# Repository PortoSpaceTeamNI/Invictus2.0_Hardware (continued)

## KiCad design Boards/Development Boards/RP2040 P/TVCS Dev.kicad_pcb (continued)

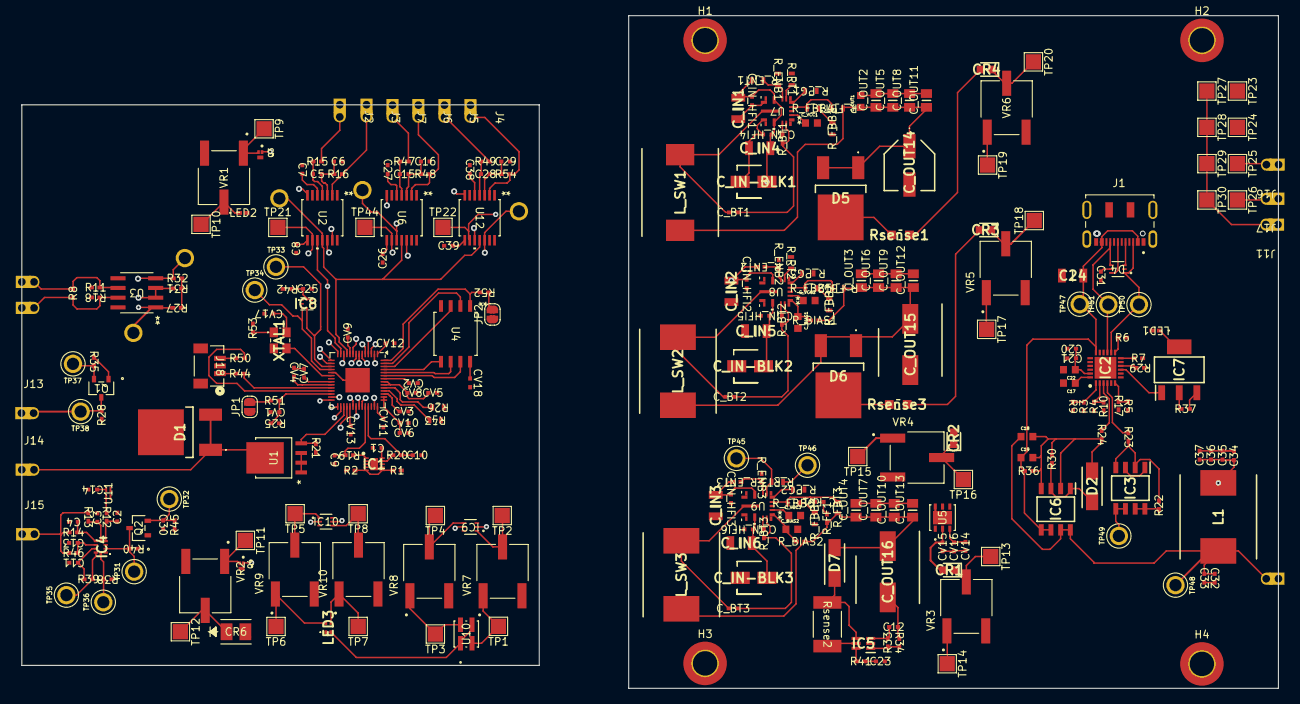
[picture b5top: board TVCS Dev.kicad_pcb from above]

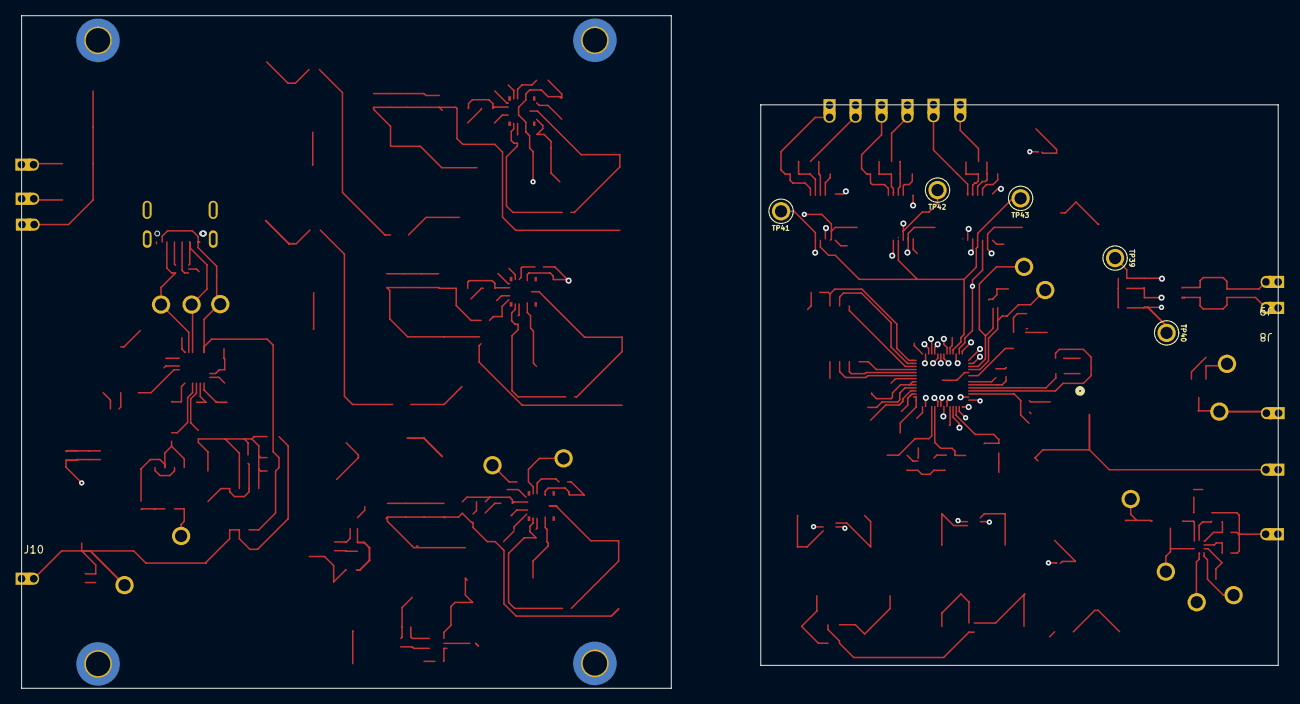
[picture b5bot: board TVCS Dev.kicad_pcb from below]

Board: 6 copper layers, 164.4 x 88.0 mm, 311 parts (8 on the bottom side), 154 nets.

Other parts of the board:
JP1, JP2: Jumper_2_Open; SolderJumper-2_P1.3mm_Open_RoundedPad1.0x1.5mm
R8: 120; RES_0402

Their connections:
/RP2040 Standard1/~RST: JP1.2 (B); also elsewhere on the board
/RP2040 Standard1/~USB_BOOT: JP2.2 (B); also elsewhere on the board
/RS_A: R8.2; also elsewhere on the board
/RS_B: R8.1; also elsewhere on the board
GND: JP1.1 (A), JP2.1 (A); also elsewhere on the board

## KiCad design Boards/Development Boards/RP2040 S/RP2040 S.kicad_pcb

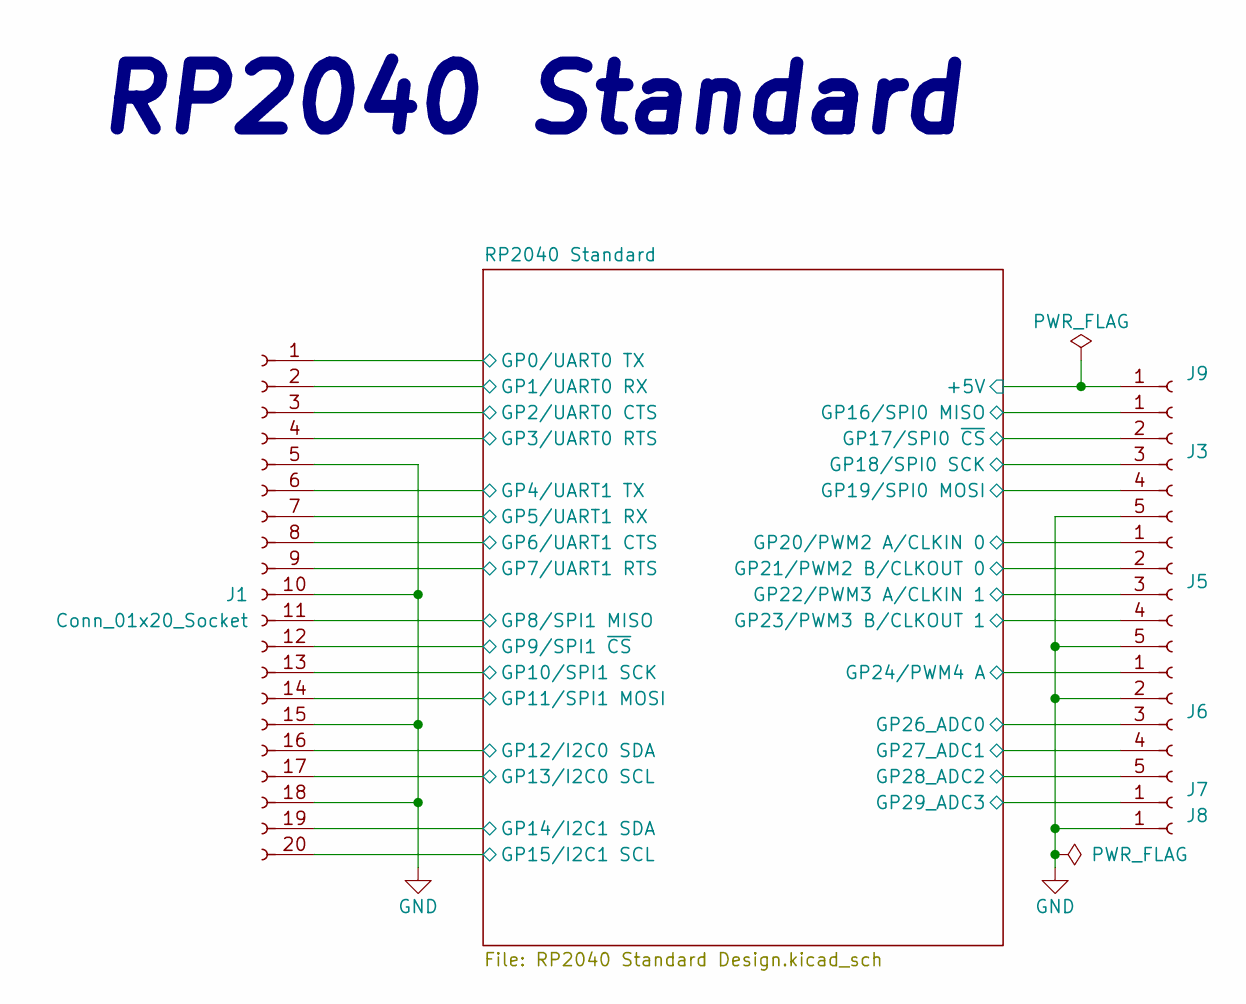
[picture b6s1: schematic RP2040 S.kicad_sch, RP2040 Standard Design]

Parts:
J1: Conn_01x20_Socket; Pico_20pin
J3, J5, J6: Conn_01x05_Socket; Pico_05pin
J7, J8, J9: Conn_01x01_Socket; Pico_01pin

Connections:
/RP2040 Standard/+5V: J9.1; also elsewhere on the board
/RP2040 Standard/GP0/UART0 TX: J1.1; also elsewhere on the board
/RP2040 Standard/GP1/UART0 RX: J1.2; also elsewhere on the board
/RP2040 Standard/GP2/UART0 CTS: J1.3; also elsewhere on the board
/RP2040 Standard/GP3/UART0 RTS: J1.4; also elsewhere on the board
/RP2040 Standard/GP4/UART1 TX: J1.6; also elsewhere on the board
/RP2040 Standard/GP5/UART1 RX: J1.7; also elsewhere on the board
/RP2040 Standard/GP6/UART1 CTS: J1.8; also elsewhere on the board
/RP2040 Standard/GP7/UART1 RTS: J1.9; also elsewhere on the board
/RP2040 Standard/GP8/SPI1 MISO: J1.11; also elsewhere on the board
/RP2040 Standard/GP9/SPI1 ~CS: J1.12; also elsewhere on the board
/RP2040 Standard/GP10/SPI1 SCK: J1.13; also elsewhere on the board
/RP2040 Standard/GP11/SPI1 MOSI: J1.14; also elsewhere on the board
/RP2040 Standard/GP12/I2C0 SDA: J1.16; also elsewhere on the board
/RP2040 Standard/GP13/I2C0 SCL: J1.17; also elsewhere on the board
/RP2040 Standard/GP14/I2C1 SDA: J1.19; also elsewhere on the board
/RP2040 Standard/GP15/I2C1 SCL: J1.20; also elsewhere on the board
/RP2040 Standard/GP16/SPI0 MISO: J3.1; also elsewhere on the board
/RP2040 Standard/GP17/SPI0 ~CS: J3.2; also elsewhere on the board
/RP2040 Standard/GP18/SPI0 SCK: J3.3; also elsewhere on the board
/RP2040 Standard/GP19/SPI0 MOSI: J3.4; also elsewhere on the board
/RP2040 Standard/GP20/PWM2 A/CLKIN 0: J5.1; also elsewhere on the board
/RP2040 Standard/GP21/PWM2 B/CLKOUT 0: J5.2; also elsewhere on the board
/RP2040 Standard/GP22/PWM3 A/CLKIN 1: J5.3; also elsewhere on the board
/RP2040 Standard/GP23/PWM3 B/CLKOUT 1: J5.4; also elsewhere on the board
/RP2040 Standard/GP24/PWM4 A: J6.1; also elsewhere on the board
/RP2040 Standard/GP26_ADC0: J6.3; also elsewhere on the board
/RP2040 Standard/GP27_ADC1: J6.4; also elsewhere on the board
/RP2040 Standard/GP28_ADC2: J6.5; also elsewhere on the board
/RP2040 Standard/GP29_ADC3: J7.1; also elsewhere on the board
GND: J1.5, J1.10, J1.15, J1.18, J3.5, J5.5, J6.2, J8.1; also elsewhere on the board

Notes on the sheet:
RP2040 Standard

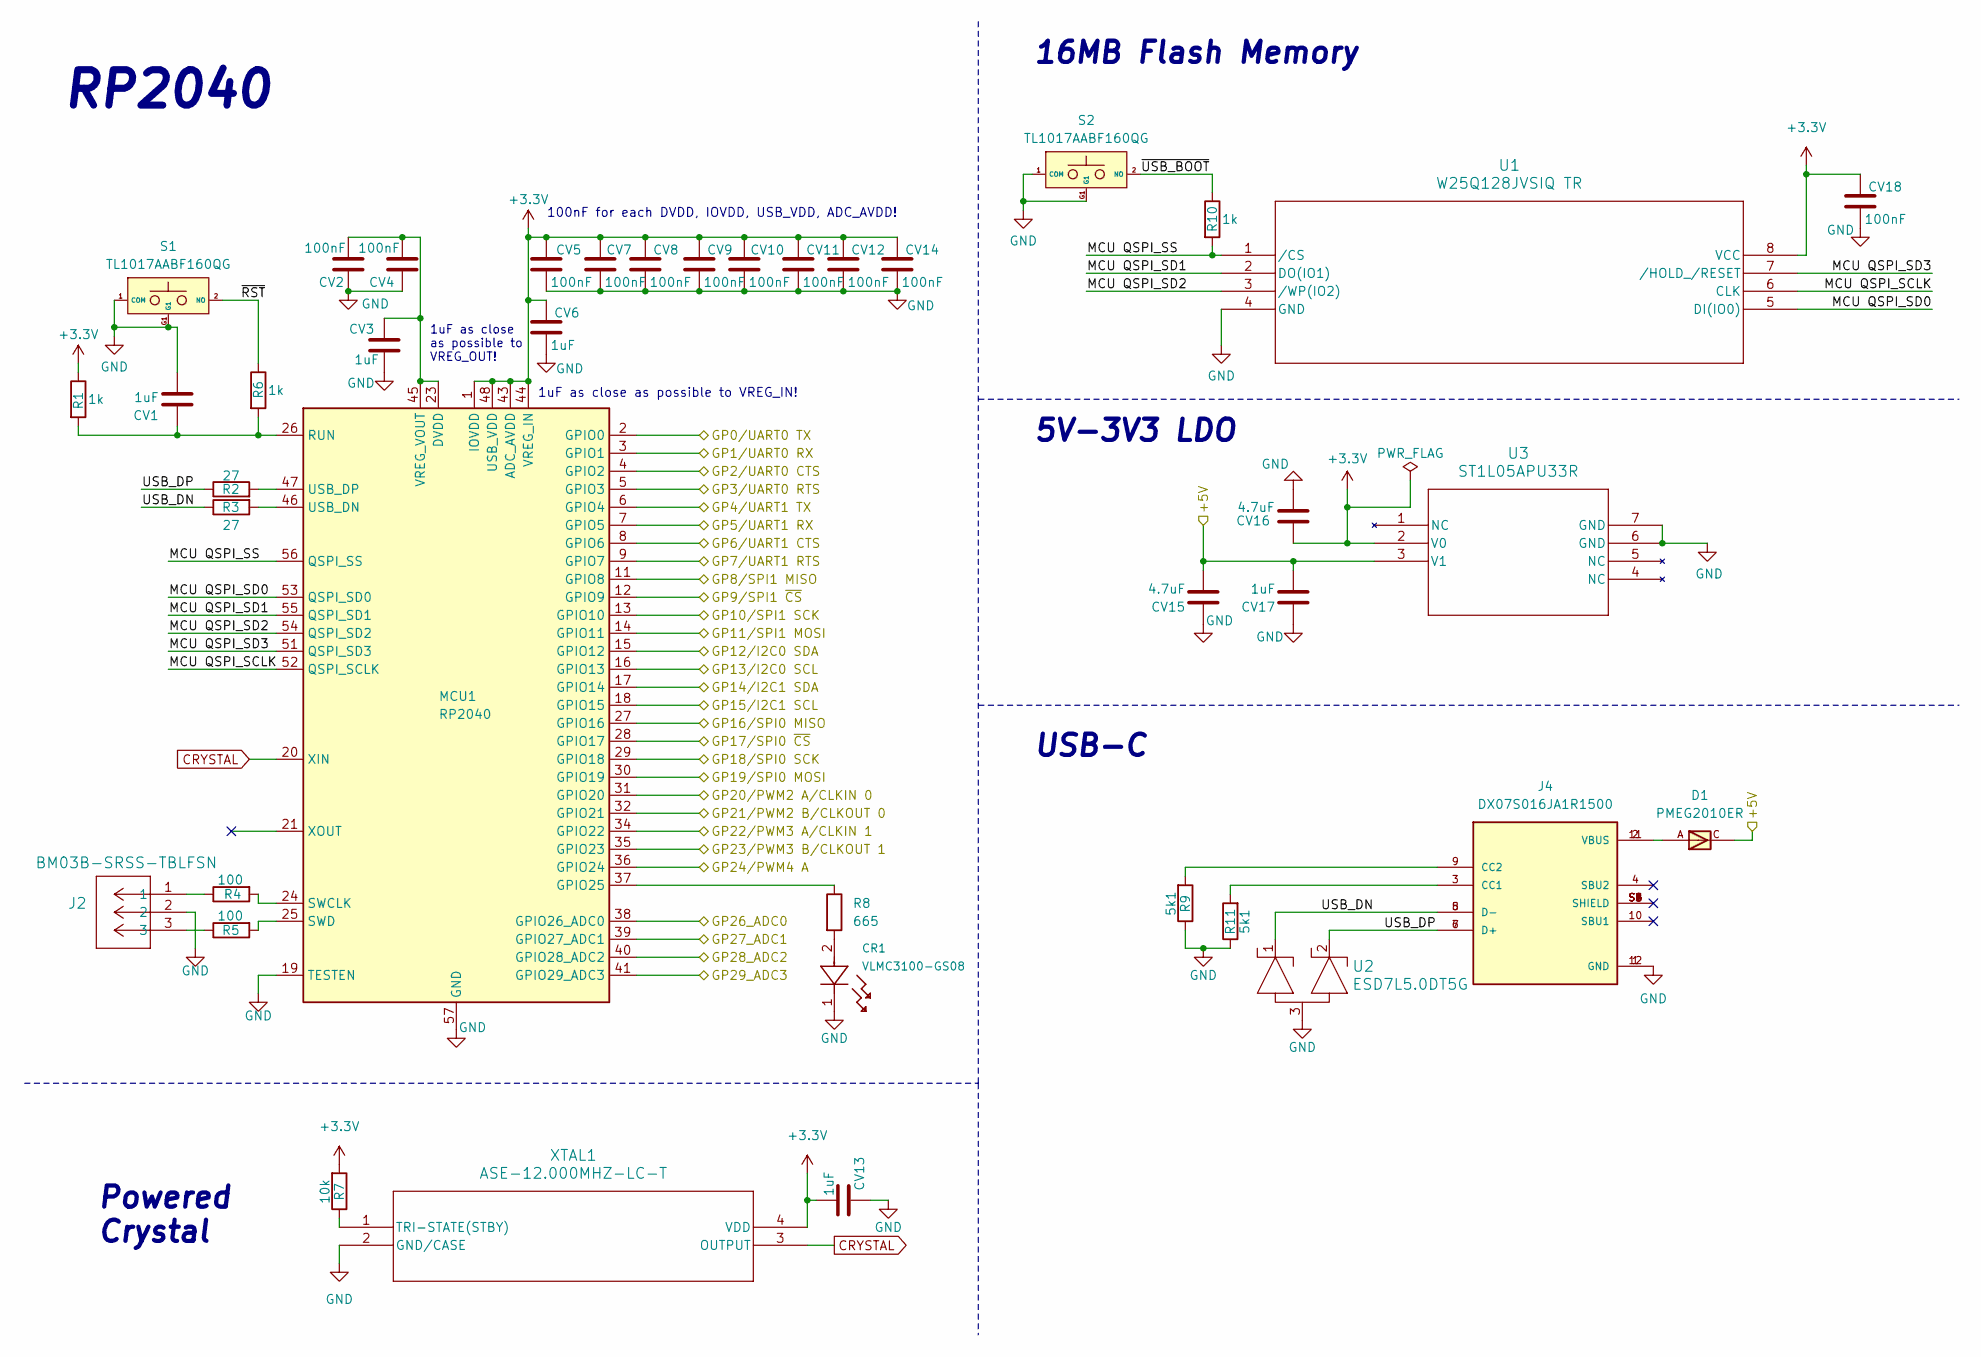
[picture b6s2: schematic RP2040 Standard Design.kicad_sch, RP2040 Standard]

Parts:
CR1: VLMC3100-GS08; LED_PLCC_VSMB
CV1, CV3, CV6, CV13, CV17: 1uF; Capacitor_0402
CV2, CV4, CV5, CV7, CV8, CV9, CV10, CV11, CV12, CV14, CV18: 100nF; Capacitor_0402
CV15, CV16: 4.7uF; Capacitor_0402
D1: PMEG2010ER; SODFL3517X110N; PARTREV 01
J2: BM03B-SRSS-TBLFSN; CONN_BM03B-SRSS-TBLFSN_JST
J4: DX07S016JA1R1500; JAE_DX07S016JA1R1500; PARTREV 1
MCU1: RP2040; QFN-56-1EP_7x7mm_P0.4mm_EP3.2x3.2mm
R1, R6, R10: 1k; RES_0402
R2, R3: 27; RES_0603
R4, R5: 100; RES_0402
R7: 10k; RES_0402
R8: 665; RES_0402
R9, R11: 5k1; RES_0402
S1, S2: TL1017AABF160QG; Mouser Part Number 612-TL1017AABF160QG
U1: W25Q128JVSIQ TR; SOIC_208MIL_WIN
U2: ESD7L5.0DT5G; SOT-723_0P85X1P25_ONS
U3: ST1L05APU33R; DFN_5APU33R_STM
XTAL1: ASE-12.000MHZ-LC-T; ASE24576MHZLCT

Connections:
+3.3V: CV5.1, CV6.1, CV7.1, CV8.1, CV9.1, CV10.1, CV11.1, CV12.1, CV13.1, CV14.1, CV16.2, CV18.1, MCU1.1 (IOVDD), MCU1.10 (IOVDD), MCU1.22 (IOVDD), MCU1.33 (IOVDD), MCU1.42 (IOVDD), MCU1.43 (ADC_AVDD), MCU1.44 (VREG_IN), MCU1.48 (USB_VDD), MCU1.49 (IOVDD), R1.1, R7.2, U1.8 (VCC), U3.2 (V0), XTAL1.4 (VDD)
/RP2040 Standard/+5V: CV15.2, CV17.2, D1.C, U3.3 (V1); also elsewhere on the board
/RP2040 Standard/GP0/UART0 TX: MCU1.2 (GPIO0); also elsewhere on the board
/RP2040 Standard/GP1/UART0 RX: MCU1.3 (GPIO1); also elsewhere on the board
/RP2040 Standard/GP2/UART0 CTS: MCU1.4 (GPIO2); also elsewhere on the board
/RP2040 Standard/GP3/UART0 RTS: MCU1.5 (GPIO3); also elsewhere on the board
/RP2040 Standard/GP4/UART1 TX: MCU1.6 (GPIO4); also elsewhere on the board
/RP2040 Standard/GP5/UART1 RX: MCU1.7 (GPIO5); also elsewhere on the board
/RP2040 Standard/GP6/UART1 CTS: MCU1.8 (GPIO6); also elsewhere on the board
/RP2040 Standard/GP7/UART1 RTS: MCU1.9 (GPIO7); also elsewhere on the board
/RP2040 Standard/GP8/SPI1 MISO: MCU1.11 (GPIO8); also elsewhere on the board
/RP2040 Standard/GP9/SPI1 ~CS: MCU1.12 (GPIO9); also elsewhere on the board
/RP2040 Standard/GP10/SPI1 SCK: MCU1.13 (GPIO10); also elsewhere on the board
/RP2040 Standard/GP11/SPI1 MOSI: MCU1.14 (GPIO11); also elsewhere on the board
/RP2040 Standard/GP12/I2C0 SDA: MCU1.15 (GPIO12); also elsewhere on the board
/RP2040 Standard/GP13/I2C0 SCL: MCU1.16 (GPIO13); also elsewhere on the board
/RP2040 Standard/GP14/I2C1 SDA: MCU1.17 (GPIO14); also elsewhere on the board
/RP2040 Standard/GP15/I2C1 SCL: MCU1.18 (GPIO15); also elsewhere on the board
/RP2040 Standard/GP16/SPI0 MISO: MCU1.27 (GPIO16); also elsewhere on the board
/RP2040 Standard/GP17/SPI0 ~CS: MCU1.28 (GPIO17); also elsewhere on the board
/RP2040 Standard/GP18/SPI0 SCK: MCU1.29 (GPIO18); also elsewhere on the board
/RP2040 Standard/GP19/SPI0 MOSI: MCU1.30 (GPIO19); also elsewhere on the board
/RP2040 Standard/GP20/PWM2 A/CLKIN 0: MCU1.31 (GPIO20); also elsewhere on the board
/RP2040 Standard/GP21/PWM2 B/CLKOUT 0: MCU1.32 (GPIO21); also elsewhere on the board
/RP2040 Standard/GP22/PWM3 A/CLKIN 1: MCU1.34 (GPIO22); also elsewhere on the board
/RP2040 Standard/GP23/PWM3 B/CLKOUT 1: MCU1.35 (GPIO23); also elsewhere on the board
/RP2040 Standard/GP24/PWM4 A: MCU1.36 (GPIO24); also elsewhere on the board
/RP2040 Standard/GP26_ADC0: MCU1.38 (GPIO26_ADC0); also elsewhere on the board
/RP2040 Standard/GP27_ADC1: MCU1.39 (GPIO27_ADC1); also elsewhere on the board
/RP2040 Standard/GP28_ADC2: MCU1.40 (GPIO28_ADC2); also elsewhere on the board
/RP2040 Standard/GP29_ADC3: MCU1.41 (GPIO29_ADC3); also elsewhere on the board
/RP2040 Standard/MCU QSPI_SCLK: MCU1.52 (QSPI_SCLK), U1.6 (CLK)
/RP2040 Standard/MCU QSPI_SD0: MCU1.53 (QSPI_SD0), U1.5 (DI(IO0))
/RP2040 Standard/MCU QSPI_SD1: MCU1.55 (QSPI_SD1), U1.2 (DO(IO1))
/RP2040 Standard/MCU QSPI_SD2: MCU1.54 (QSPI_SD2), U1.3 (/WP(IO2))
/RP2040 Standard/MCU QSPI_SD3: MCU1.51 (QSPI_SD3), U1.7 (/HOLD_/RESET)
/RP2040 Standard/MCU QSPI_SS: MCU1.56 (QSPI_SS), R10.2, U1.1 (/CS)
/RP2040 Standard/USB_DN: J4.5 (D-), J4.8 (D-), R3.1, U2.1
/RP2040 Standard/USB_DP: J4.6 (D+), J4.7 (D+), R2.1, U2.2
/RP2040 Standard/~RST: R6.1, S1.2 (NO)
/RP2040 Standard/~USB_BOOT: R10.1, S2.2 (NO)
CRYSTAL: MCU1.20 (XIN), XTAL1.3 (OUTPUT)
GND: CR1.1, CV1.2, CV2.1, CV3.2, CV4.1, CV5.2, CV6.2, CV7.2, CV8.2, CV9.2, CV10.2, CV11.2, CV12.2, CV13.2, CV14.2, CV15.1, CV16.1, CV17.1, CV18.2, J2.2, J4.1 (GND), J4.12 (GND), MCU1.19 (TESTEN), MCU1.57 (GND), R9.1, R11.1, S1.1 (COM), S1.G1, S2.1 (COM), S2.G1, U1.4 (GND), U2.3, U3.6 (GND), U3.7 (GND), XTAL1.2 (GND/CASE); also elsewhere on the board
unnamed: CR1.2, R8.2
unnamed: D1.A, J4.2 (VBUS), J4.11 (VBUS)
unnamed: J2.1, R4.1
unnamed: J2.3, R5.1
unnamed: J4.3 (CC1), R11.2
unnamed: J4.9 (CC2), R9.2
unnamed: MCU1.37 (GPIO25), R8.1
unnamed: CV1.1, MCU1.26 (RUN), R1.2, R6.2
unnamed: MCU1.24 (SWCLK), R4.2
unnamed: MCU1.25 (SWD), R5.2
unnamed: MCU1.46 (USB_DN), R3.2
unnamed: MCU1.47 (USB_DP), R2.2
unnamed: CV2.2, CV3.1, CV4.2, MCU1.23 (DVDD), MCU1.45 (VREG_VOUT), MCU1.50 (DVDD)
unnamed: R7.1, XTAL1.1 (TRI-STATE(STBY))

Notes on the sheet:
USB-C
5V-3V3 LDO
16MB Flash Memory
Powered Crystal
1uF as close as possible to VREG_OUT!
100nF for each DVDD, IOVDD, USB_VDD, ADC_AVDD!
1uF as close as possible to VREG_IN!
RP2040

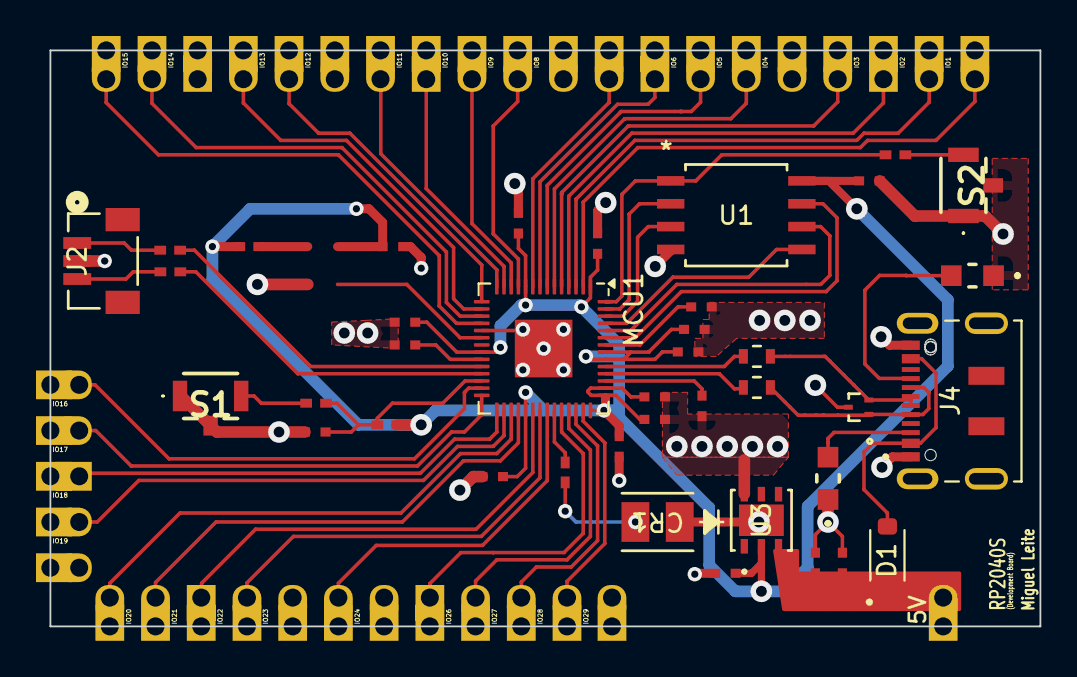
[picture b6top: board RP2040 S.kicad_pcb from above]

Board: 4 copper layers, 55.0 x 32.0 mm, 46 parts (0 on the bottom side), 55 nets.

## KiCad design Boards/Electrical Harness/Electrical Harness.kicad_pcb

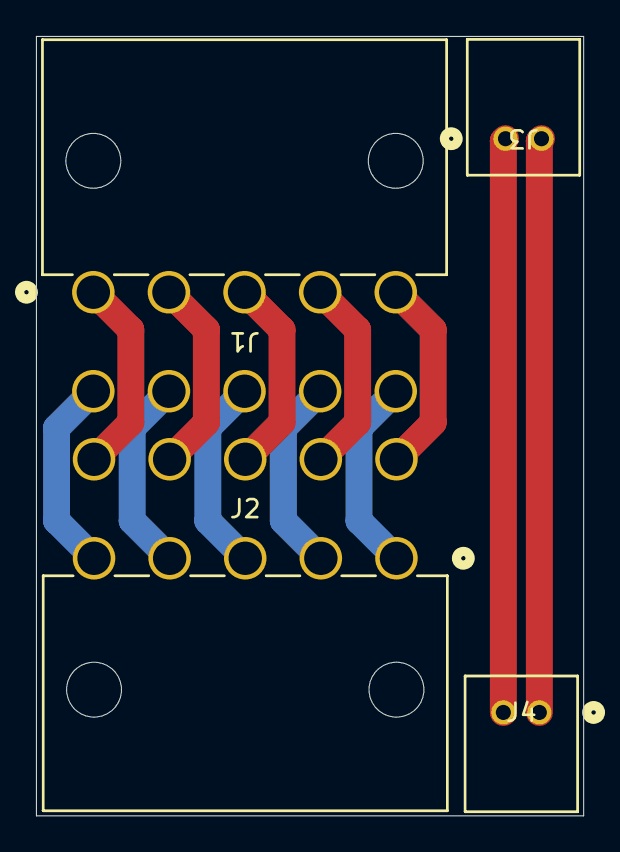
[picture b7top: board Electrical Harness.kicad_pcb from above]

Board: 4 copper layers, 30.4 x 43.3 mm, 4 parts (0 on the bottom side), 12 nets.

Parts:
J1, J2: 39300100; CONN_5569-10A_MOL
J3, J4: 532540270; CONN02_532540270_MOL

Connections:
unnamed: J1.1, J2.10
unnamed: J1.2, J2.9
unnamed: J1.3, J2.8
unnamed: J1.4, J2.7
unnamed: J1.5, J2.6
unnamed: J1.6, J2.5
unnamed: J1.7, J2.4
unnamed: J1.8, J2.3
unnamed: J1.9, J2.2
unnamed: J1.10, J2.1
unnamed: J3.1, J4.2
unnamed: J3.2, J4.1
